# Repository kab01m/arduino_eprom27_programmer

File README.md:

# EPROM 27-series Arduino-based programmer

Work in-progress of a project of easy-to-use programmer for EPROM 27-series based on Arduino.

*Download GUI application and Arduino sketch from "Releases".*

Supported chips:
 * 27C16 (connects from 3 to 26 leg DIP28 socket)
 * 27C32 (connects from 3 to 26 leg DIP28 socket)
 * 27C64
 * 27C128
 * 27C256
 * 27C512
 * Dallas DS1225 NVRAM

## Installation

Order PCB from gerber files, assemble the board. Use BOM to find components.

If non-Arduino MCU was used you have to flash bootloader from Arduino IDE using ICSP connector. 

If first time assembled you have to load sketch.ino into Arduino IDE and flash your Arduino.

Always check programming voltage before inserting new chip to program.

Run GUI application and choose serial port.

## Schematics

[Initial project](<https://github.com/bouletmarc/BMBurner>):
* Was made in DIP packages.
* No sources.
* Windows-only application.

[Walhi project](<https://github.com/walhi/arduino_eprom27_programmer>):
* Made in Eagle.
* 50/50 SMD/DIP.
* New Arduino sources.
* Windows/Linux Qt-based light GUI application.

[Radionews fork](<https://github.com/Radionews/arduino_eprom27_programmer>):
* Refactored in EasyEDA.
* Uses SPI for logic.
* Mostly SMD components.
* Uses GUI application from above.

[This project](<https://github.com/kab01m/arduino_eprom27_programmer>):
* Translated to KiCad EDA.
* SMD components whereever it was possible.
* Arduino is now not detachable.
* No schematic difference from above.
* Previous software used.

Schematics

Assembled picture

## Software

Software is taken from [Walhi project](<https://github.com/walhi/arduino_eprom27_programmer>).

Functions:

 * Read EEPROM/NVRAM.
 * Write EEPROM/NVRAM.
 * Verify chip and check if it is zeroed.
 * Programming voltage check (available for AVR in TQFP case)

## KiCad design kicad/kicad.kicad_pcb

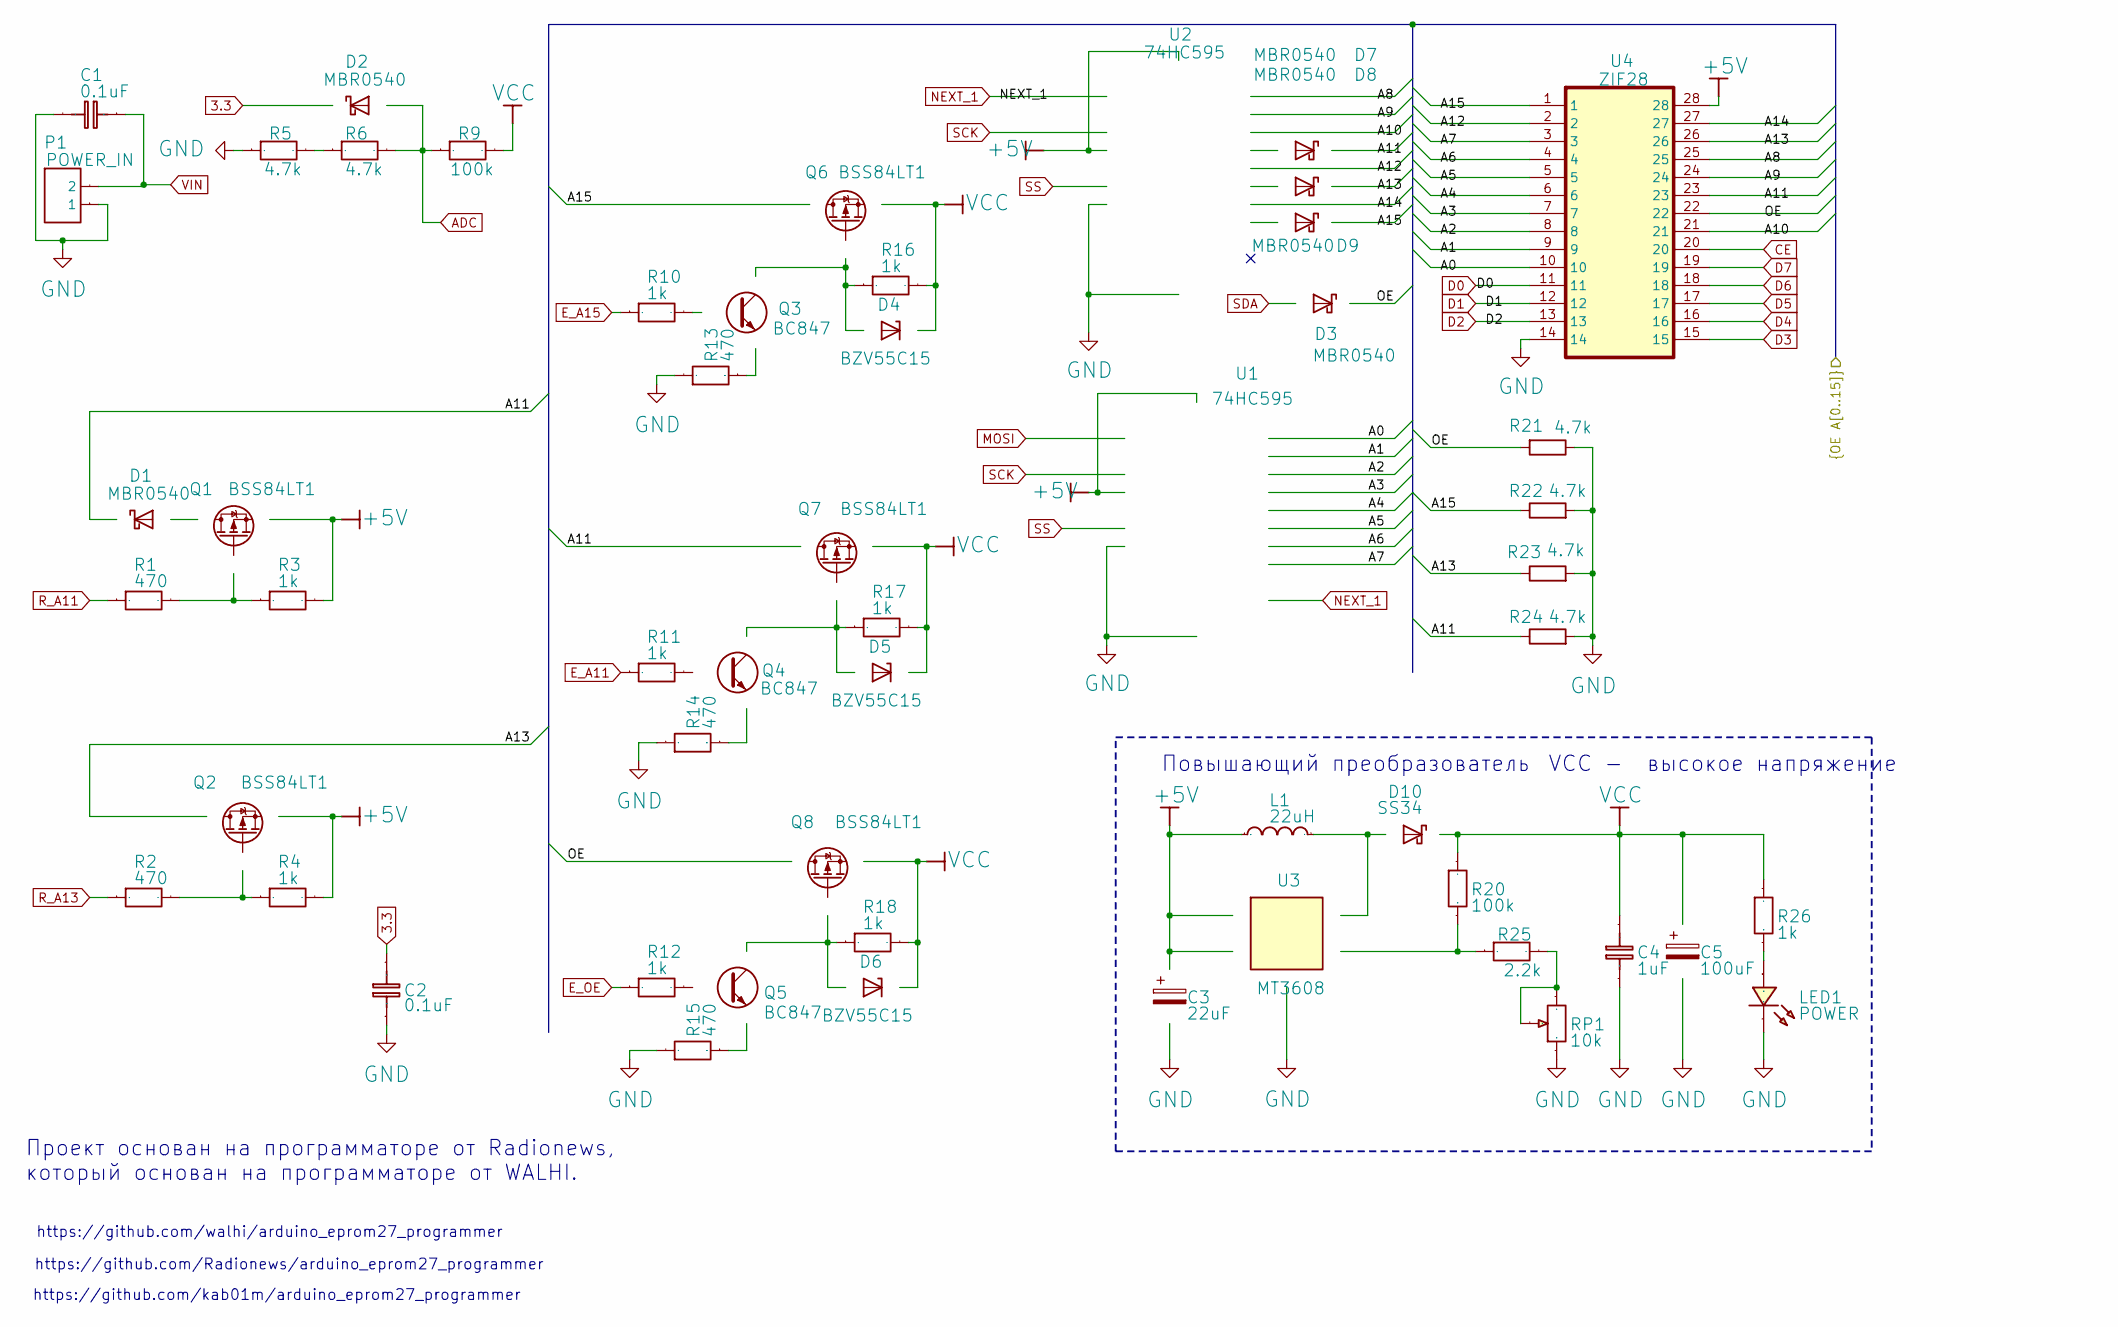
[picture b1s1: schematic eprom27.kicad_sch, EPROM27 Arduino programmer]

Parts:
C1, C2: 0.1uF; C_0805_2012Metric_Pad1.18x1.45mm_HandSolder
C3: 22uF; CP_Elec_5x5.4
C4: 1uF; C_1206_3216Metric_Pad1.33x1.80mm_HandSolder
C5: 100uF; CP_Elec_8x6.2
D1, D2, D3, D7, D8, D9: MBR0540; D_SOD-123
D4, D5, D6: BZV55C15; D_MiniMELF
D10: SS34; D_SMA
L1: 22uH; L_Chilisin_BMRx00060630
LED1: POWER; LED_0805_2012Metric_Pad1.15x1.40mm_HandSolder
P1: POWER_IN; JST_NV_B02P-NV_1x02_P5.00mm_Vertical
Q1, Q2, Q6, Q7, Q8: BSS84LT1; SOT-23
Q3, Q4, Q5: BC847; SOT-23
R1, R2, R13, R14, R15: 470; R_0805_2012Metric_Pad1.20x1.40mm_HandSolder
R3, R4, R10, R11, R12, R16, R17, R18, R26: 1k; R_0805_2012Metric_Pad1.20x1.40mm_HandSolder
R5, R6, R21, R22, R23, R24: 4.7k; R_0805_2012Metric_Pad1.20x1.40mm_HandSolder
R9, R20: 100k; R_0805_2012Metric_Pad1.20x1.40mm_HandSolder
R25: 2.2k; R_0805_2012Metric_Pad1.20x1.40mm_HandSolder
RP1: 10k; Potentiometer_Bourns_3224W_Vertical
U1, U2: 74HC595; SOIC-16_3.9x9.9mm_P1.27mm
U3: MT3608; SOT-23-6
U4: ZIF28; DIP_Socket-28_W11.9_W12.7_W15.24_W17.78_W18.5_3M_228-1277-0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

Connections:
3.3: C2.2, D2.1 (K); also elsewhere on the board
+5V: C3.1, L1.1, Q1.2 (S), Q2.2 (S), R3.2, R4.2, U1.10 (~SRCLR), U1.16 (VCC), U2.10 (~SRCLR), U2.16 (VCC), U3.4 (EN), U3.5 (IN), U4.28; also elsewhere on the board
/EPROM27/A0: U1.15 (QA), U4.10
/EPROM27/A1: U1.1 (QB), U4.9
/EPROM27/A2: U1.2 (QC), U4.8
/EPROM27/A3: U1.3 (QD), U4.7
/EPROM27/A4: U1.4 (QE), U4.6
/EPROM27/A5: U1.5 (QF), U4.5
/EPROM27/A6: U1.6 (QG), U4.4
/EPROM27/A7: U1.7 (QH), U4.3
/EPROM27/A8: U2.15 (QA), U4.25
/EPROM27/A9: U2.1 (QB), U4.24
/EPROM27/A10: U2.2 (QC), U4.21
/EPROM27/A11: D1.1 (K), D7.1 (K), Q7.3 (D), R24.1, U4.23
/EPROM27/A12: U2.4 (QE), U4.2
/EPROM27/A13: D8.1 (K), Q2.3 (D), R23.1, U4.26
/EPROM27/A14: U2.6 (QG), U4.27
/EPROM27/A15: D9.1 (K), Q6.3 (D), R22.1, U4.1
/EPROM27/OE: D3.1 (K), Q8.3 (D), R21.2, U4.22
ADC: D2.2 (A), R6.2, R9.1; also elsewhere on the board
CE: U4.20; also elsewhere on the board
D0: U4.11; also elsewhere on the board
D1: U4.12; also elsewhere on the board
D2: U4.13; also elsewhere on the board
D3: U4.15; also elsewhere on the board
D4: U4.16; also elsewhere on the board
D5: U4.17; also elsewhere on the board
D6: U4.18; also elsewhere on the board
D7: U4.19; also elsewhere on the board
E_A11: R11.1; also elsewhere on the board
E_A15: R10.1; also elsewhere on the board
E_OE: R12.1; also elsewhere on the board
MISO: R1.1; also elsewhere on the board
MOSI: U1.14 (SER); also elsewhere on the board
NEXT_1: U1.9 (QH'), U2.14 (SER)
unnamed: D1.2 (A), Q1.3 (D)
unnamed: D4.2 (A), Q3.3 (C), Q6.1 (G), R16.1
unnamed: D5.2 (A), Q4.3 (C), Q7.1 (G), R17.1
unnamed: D6.2 (A), Q5.3 (C), Q8.1 (G), R18.1
unnamed: D7.2 (A), U2.3 (QD)
unnamed: D8.2 (A), U2.5 (QF)
unnamed: D9.2 (A), U2.7 (QH)
unnamed: D10.2 (A), L1.2, U3.1 (SW)
unnamed: LED1.1, R26.1
unnamed: Q1.1 (G), R1.2, R3.1
unnamed: Q2.1 (G), R2.2, R4.1
unnamed: Q3.1 (B), R10.2
unnamed: Q3.2 (E), R13.1
unnamed: Q4.1 (B), R11.2
unnamed: Q4.2 (E), R14.1
unnamed: Q5.1 (B), R12.2
unnamed: Q5.2 (E), R15.1
unnamed: R5.2, R6.1
unnamed: R25.2, RP1.2, RP1.3
unnamed: R20.1, R25.1, U3.3 (FB)
R_A13: R2.1; also elsewhere on the board
SCK: U1.11 (SRCLK), U2.11 (SRCLK); also elsewhere on the board
SDA: D3.2 (A); also elsewhere on the board
SS: U1.12 (RCLK), U2.12 (RCLK); also elsewhere on the board
VCC: C4.2, C5.1, D4.1 (K), D5.1 (K), D6.1 (K), D10.1 (K), Q6.2 (S), Q7.2 (S), Q8.2 (S), R9.2, R16.2, R17.2, R18.2, R20.2, R26.2
VIN: C1.1, P1.2; also elsewhere on the board

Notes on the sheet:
https://github.com/walhi/arduino_eprom27_programmer
Проект основан на программаторе от Radionews, который основан на программаторе от WALHI.
VCC - высокое напряжение
Повышающий преобразователь
https://github.com/Radionews/arduino_eprom27_programmer
https://github.com/kab01m/arduino_eprom27_programmer

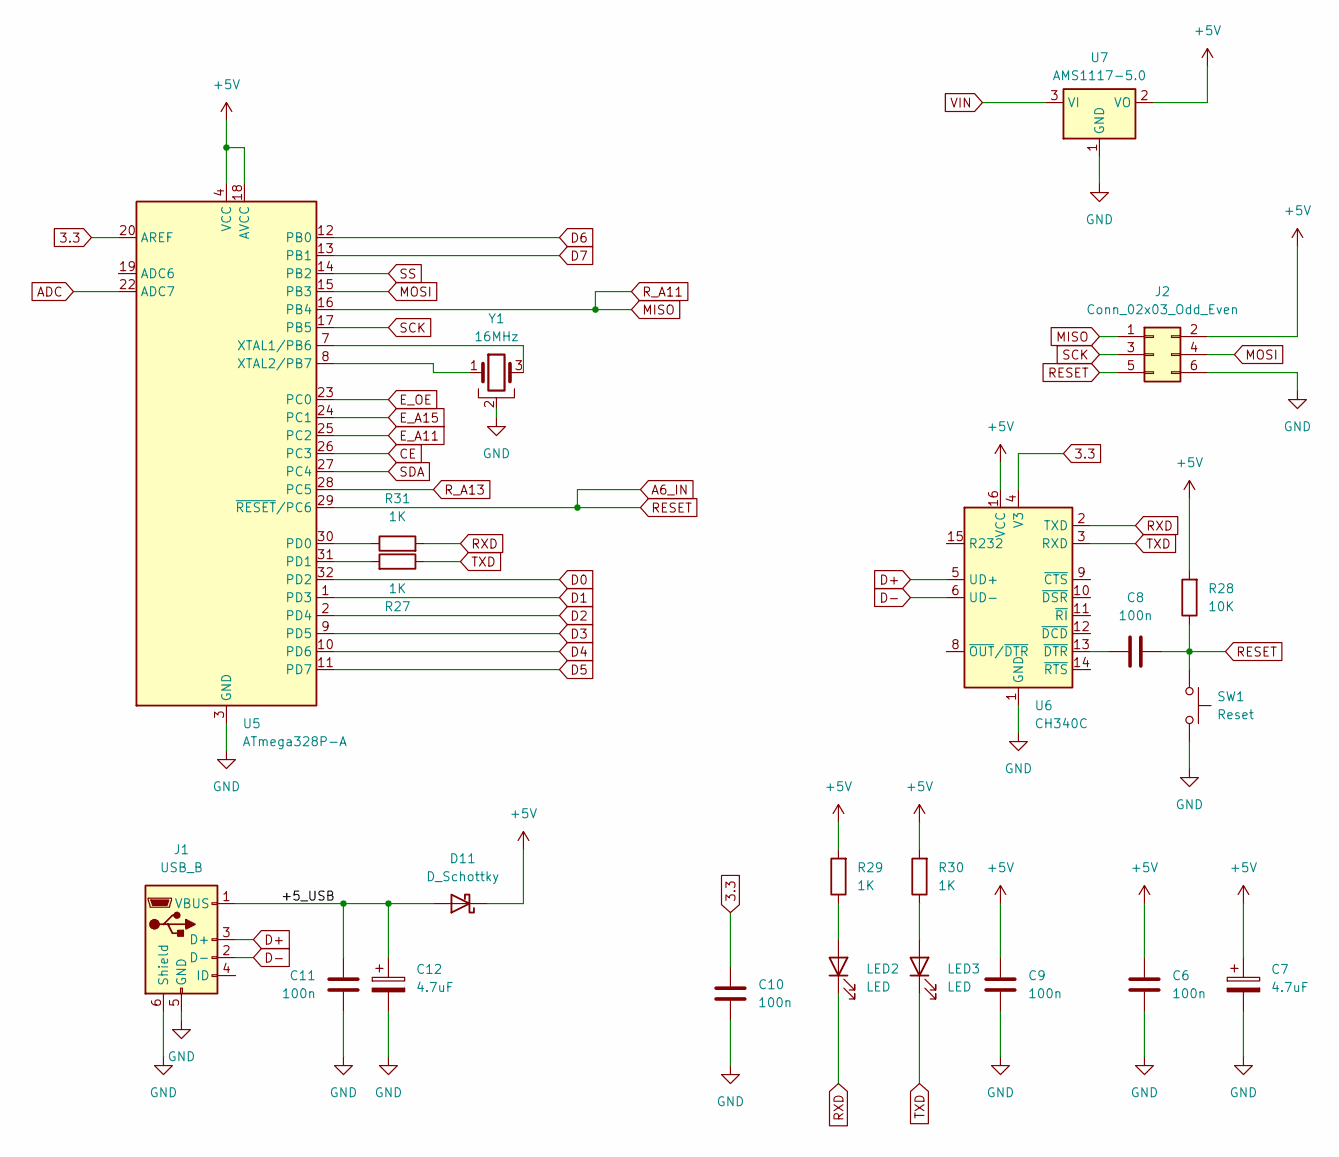
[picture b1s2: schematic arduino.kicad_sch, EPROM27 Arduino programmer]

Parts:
C6, C8, C9, C10, C11: 100n; C_0805_2012Metric_Pad1.18x1.45mm_HandSolder
C7, C12: 4.7uF; CP_EIA-3216-18_Kemet-A_Pad1.58x1.35mm_HandSolder
D11: D_Schottky; D_SOD-323_HandSoldering
J1: USB_B; USB_Mini-B_Lumberg_2486_01_Horizontal
J2: Conn_02x03_Odd_Even; PinHeader_2x03_P2.54mm_Vertical
LED2, LED3: LED; LED_0805_2012Metric_Pad1.15x1.40mm_HandSolder
R27, R29, R30, R31: 1K; R_0805_2012Metric_Pad1.20x1.40mm_HandSolder
R28: 10K; R_0805_2012Metric_Pad1.20x1.40mm_HandSolder
SW1: Reset; SW_SPST_TL3342
U5: ATmega328P-A; TQFP-32_7x7mm_P0.8mm
U6: CH340C; SOIC-16_3.9x9.9mm_P1.27mm
U7: AMS1117-5.0; SOT-223-3_TabPin2
Y1: 16MHz; Resonator_SMD_Murata_CSTxExxV-3Pin_3.0x1.1mm

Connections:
3.3: C10.1, U5.20 (AREF), U6.4 (V3); also elsewhere on the board
+5V: C6.1, C7.1, C9.1, D11.1 (K), J2.2, R28.2, R29.2, R30.2, U5.4 (VCC), U5.6 (VCC), U5.18 (AVCC), U6.16 (VCC), U7.2 (VO); also elsewhere on the board
/Arduino/+5_USB: C11.1, C12.1, D11.2 (A), J1.1 (VBUS)
A6_IN: C8.2, J2.5, R28.1, SW1.1, U5.29 (~RESET/PC6)
ADC: U5.22 (ADC7); also elsewhere on the board
CE: U5.26 (PC3); also elsewhere on the board
D0: U5.32 (PD2); also elsewhere on the board
D1: U5.1 (PD3); also elsewhere on the board
D2: U5.2 (PD4); also elsewhere on the board
D3: U5.9 (PD5); also elsewhere on the board
D4: U5.10 (PD6); also elsewhere on the board
D5: U5.11 (PD7); also elsewhere on the board
D6: U5.12 (PB0); also elsewhere on the board
D7: U5.13 (PB1); also elsewhere on the board
D+: J1.3 (D+), U6.5 (UD+)
D-: J1.2 (D-), U6.6 (UD-)
E_A11: U5.25 (PC2); also elsewhere on the board
E_A15: U5.24 (PC1); also elsewhere on the board
E_OE: U5.23 (PC0); also elsewhere on the board
MISO: J2.1, U5.16 (PB4); also elsewhere on the board
MOSI: J2.4, U5.15 (PB3); also elsewhere on the board
unnamed: LED2.2 (A), R29.1
unnamed: LED3.2 (A), R30.1
unnamed: R31.1, U5.30 (PD0)
unnamed: R27.2, U5.31 (PD1)
unnamed: U5.7 (XTAL1/PB6), Y1.3
unnamed: U5.8 (XTAL2/PB7), Y1.1
unnamed: C8.1, U6.13 (~DTR)
RXD: LED2.1 (K), R31.2, U6.2 (TXD)
R_A13: U5.28 (PC5); also elsewhere on the board
SCK: J2.3, U5.17 (PB5); also elsewhere on the board
SDA: U5.27 (PC4); also elsewhere on the board
SS: U5.14 (PB2); also elsewhere on the board
TXD: LED3.1 (K), R27.1, U6.3 (RXD)
VIN: U7.3 (VI); also elsewhere on the board

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
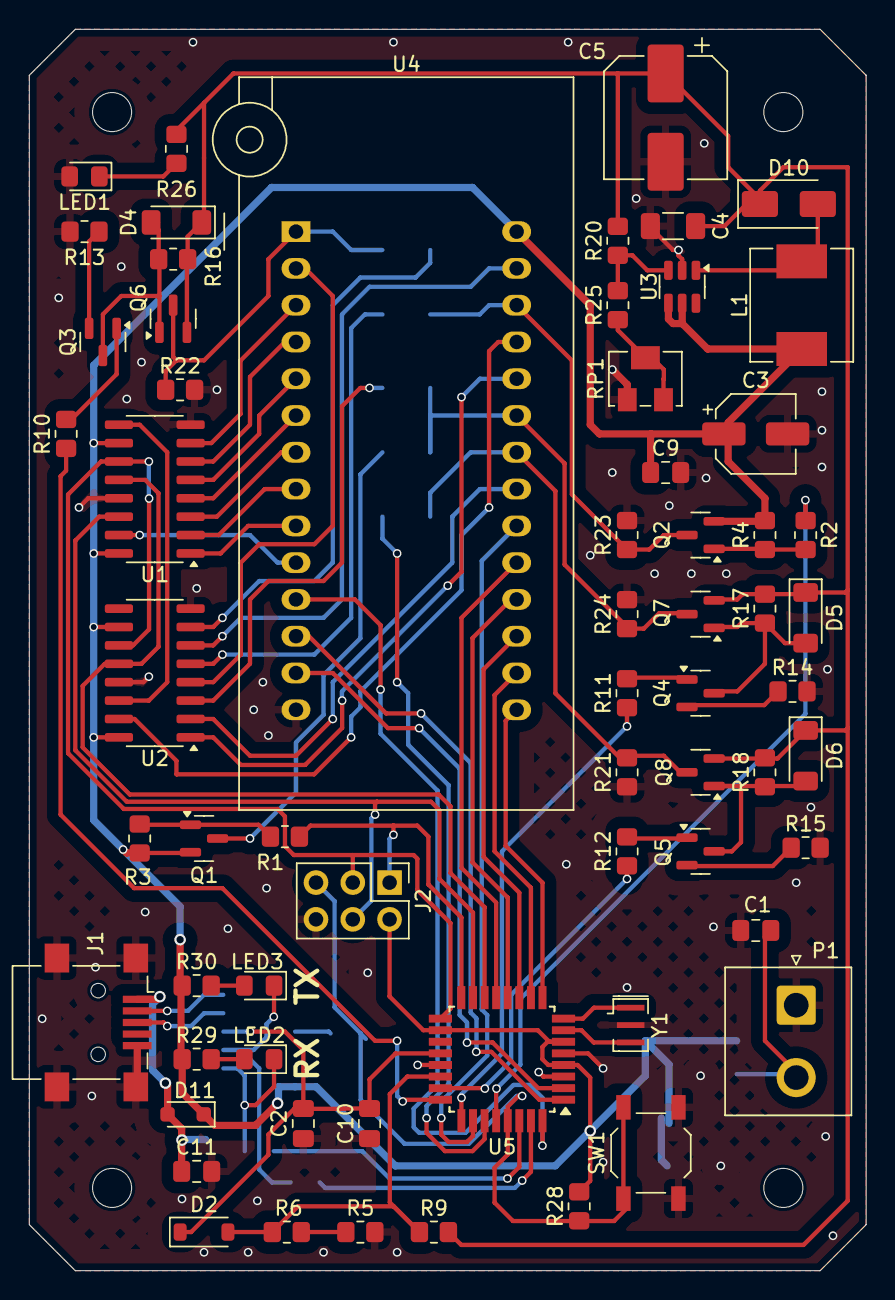
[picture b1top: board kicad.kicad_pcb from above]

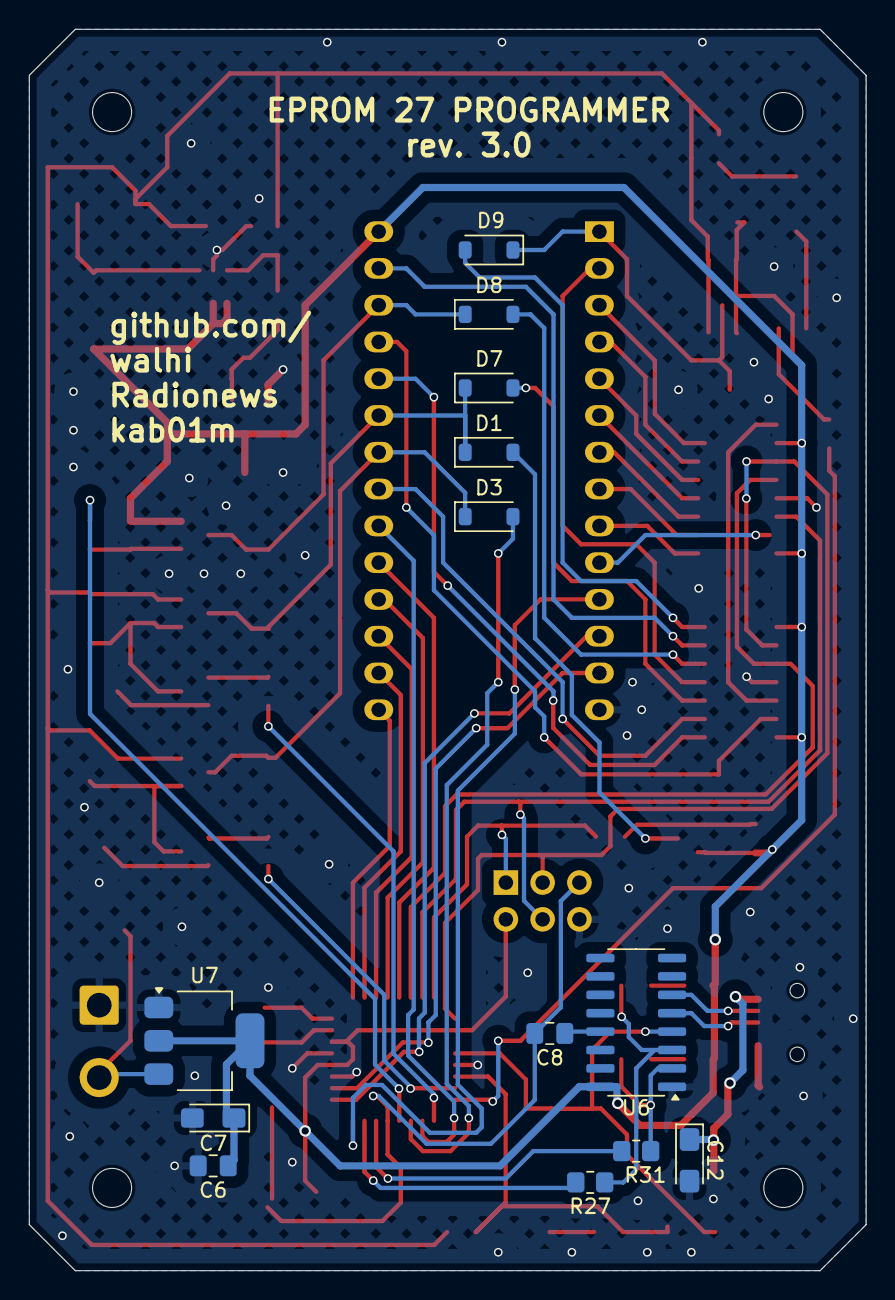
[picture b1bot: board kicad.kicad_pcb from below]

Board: 2 copper layers, 57.8 x 85.7 mm, 76 parts (13 on the bottom side), 75 nets.

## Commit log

2024-03-21 Schematics and first board
2024-04-16 Small pre-release fixes
